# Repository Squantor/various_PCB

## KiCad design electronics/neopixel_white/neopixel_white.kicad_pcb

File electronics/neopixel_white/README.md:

# Neopixel formfactor white LED
Simple white led in neopixel form factor. Sometimes you dont want a controllable RGB LED in some spots.
## TODO's
Still some things need to be done:
* update Readme.md with pictures and BOM
## BOM
* Generic white LED in 2835 package

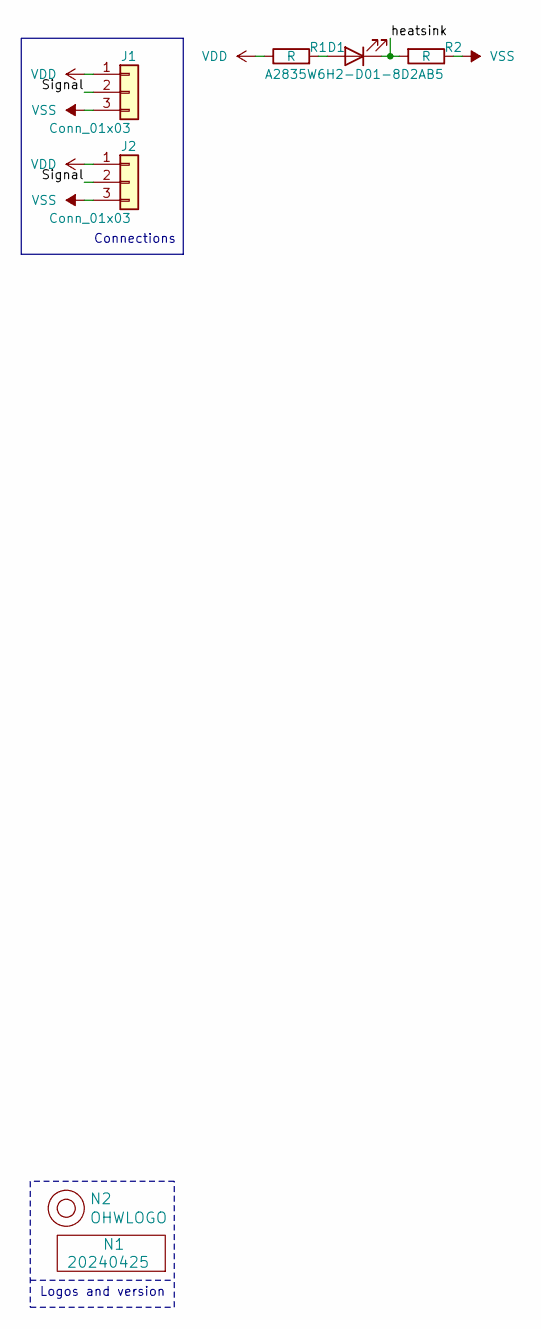
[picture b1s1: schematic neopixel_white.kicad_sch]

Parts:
D1: A2835W6H2-D01-8D2AB5; LED_2835_Hongli
J1, J2: Conn_01x03; pads-0200-1x03-W012-D020
N1: 20240425; Label_Generic
N2: OHWLOGO; OSHW-Symbol_6.7x6mm_SilkScreen
R1, R2: R; R_0805

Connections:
/Signal: J1.2, J2.2
/heatsink: D1.1 (K), R2.2
unnamed: D1.2 (A), R1.2
VDD: J1.1, J2.1, R1.1
VSS: J1.3, J2.3, R2.1

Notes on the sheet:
Connections
Logos and version

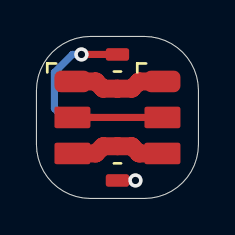
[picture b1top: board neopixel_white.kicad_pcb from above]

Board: 2 copper layers, 9.0 x 9.0 mm, 7 parts (1 on the bottom side), 5 nets.

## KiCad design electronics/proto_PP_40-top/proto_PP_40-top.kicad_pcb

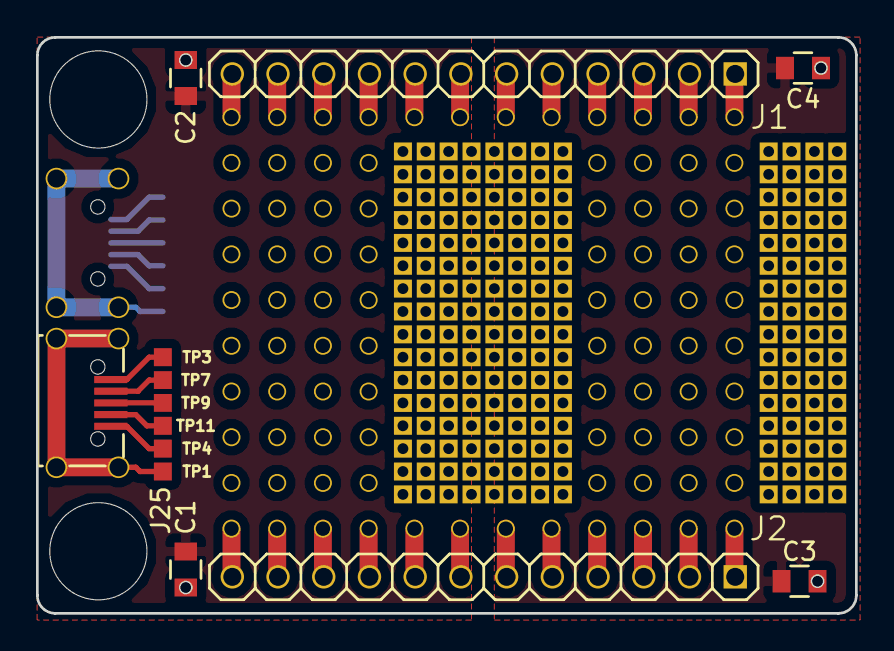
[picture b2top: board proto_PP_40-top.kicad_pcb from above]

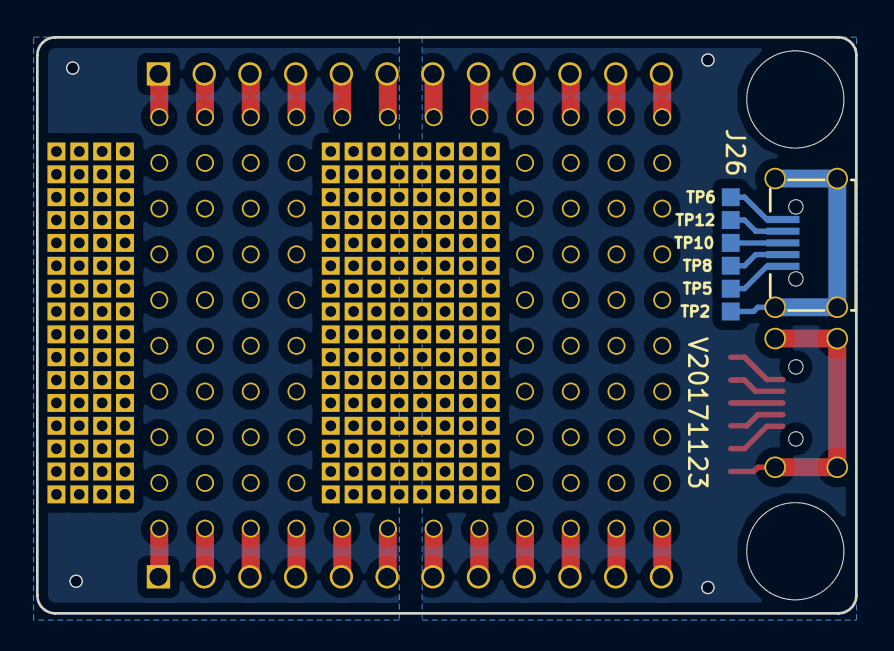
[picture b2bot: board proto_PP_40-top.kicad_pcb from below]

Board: 2 copper layers, 45.5 x 32.0 mm, 45 parts (8 on the bottom side), 40 nets.

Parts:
C1, C2, C3, C4: C; C_0805
H1, H2: Drill_Hole_no_metal; MountingHole_5.4mm_no_metal
J1, J2: PINS_1X12; Header-0254-1X12-H010
J3, J4, J7, J18, J19, J20: Proto_4pins; proto-TH-0254-04X01-P010SQ-H008
J5, J6, J9, J10, J13, J14, J16, J17, J21, J22, J23, J24: Proto; proto-SMD-0127-04X04-P010-H006
J8, J11, J12, J15: Proto; proto-TH-0254-04X04-P010SQ-H008
J25, J26: USB-ID; SquantorUsb-USB-UB-SMD4H
N2: V20171123; Label_version
TP1, TP2, TP3, TP4, TP5, TP6, TP7, TP8, TP9, TP10, TP11, TP12: testpad; TESTPAD_SQ_1MM

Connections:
GND: C1.2, C2.2
GNDA: C3.2, C4.2
unnamed: J1.1, J3.1
unnamed: J1.2, J3.2
unnamed: J1.3, J3.3
unnamed: J1.4, J3.4
unnamed: J1.5, J7.1
unnamed: J1.6, J7.2
unnamed: J1.7, J7.3
unnamed: J1.8, J7.4
unnamed: J1.9, J4.1
unnamed: J1.10, J4.2
unnamed: J1.11, J4.3
unnamed: J1.12, J4.4
unnamed: J2.9, J20.1
unnamed: J2.10, J20.2
unnamed: J2.11, J20.3
unnamed: J2.12, J20.4
unnamed: J2.5, J18.1
unnamed: J2.6, J18.2
unnamed: J2.7, J18.3
unnamed: J2.8, J18.4
unnamed: J2.1, J19.1
unnamed: J2.2, J19.2
unnamed: J2.3, J19.3
unnamed: J2.4, J19.4
unnamed: J25.1, TP3.1
unnamed: J25.2, TP7.1
unnamed: J25.3, TP9.1
unnamed: J25.4, TP11.1
unnamed: J25.5, TP4.1
unnamed: J25.S, TP1.1
unnamed: J26.1, TP5.1
unnamed: J26.2, TP8.1
unnamed: J26.3, TP10.1
unnamed: J26.4, TP12.1
unnamed: J26.5, TP6.1
unnamed: J26.S, TP2.1
VDD: C1.1, C2.1
VDDA: C3.1, C4.1

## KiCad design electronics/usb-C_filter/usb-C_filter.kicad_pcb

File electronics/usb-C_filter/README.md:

# USB-C filter
USB style filter/protection prevents communication on data lines but can also be used as USB-C to USB-A converter.
## TODO's
Still some things need to be done:
* schematic entry 
* PCB layout
* Review with one night in between
* Produce at [OSHPARK](https://oshpark.com/)
* Assemble
* Test & characterise
* update Readme.md with pictures and BOM
## BOM
* [USB-C connector from LCSC](https://lcsc.com/product-detail/USB-Connectors_Korean-Hroparts-Elec-TYPE-C-31-M-12_C165948.html)

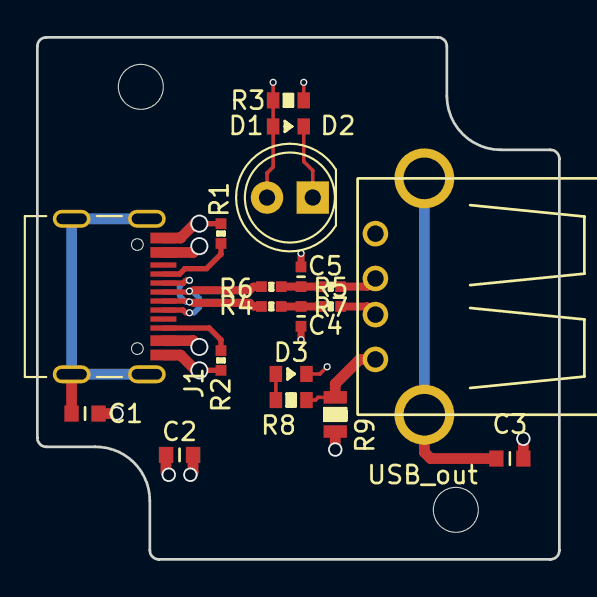
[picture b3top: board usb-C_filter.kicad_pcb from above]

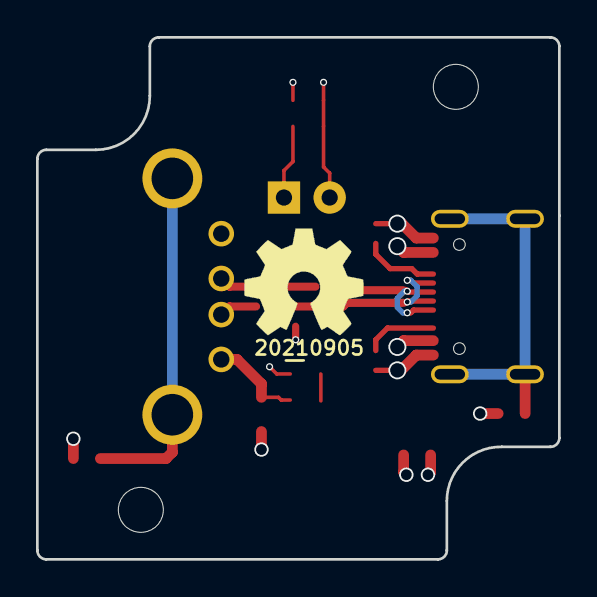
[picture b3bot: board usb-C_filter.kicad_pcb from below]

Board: 4 copper layers, 29.0 x 29.0 mm, 23 parts (2 on the bottom side), 15 nets.

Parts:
C1, C3: 10n; C_0603
C2: 100n; C_0603
C4, C5: TBD; C_0402
D1, D3: LED; LED_0603_hand
D2: LED; LED_D5.0mm
H1, H2: Drill_Hole_no_metal; MountingHole_2.5mm_no_metal
J1: USB-C_PD_USB; USB-C-HRO-31-M-12
J2: USB_out; USB-A-TH
N1: OHWLOGO; OSHW-Symbol_6.7x6mm_SilkScreen
N2: 20210905; Label_Generic
R1, R2: 5.1K; R_0402_hand
R3, R8: 1K; R_0603_hand
R4, R5, R6, R7: TBD; R_0402_hand
R9: 0; R_0805

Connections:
/CC1: J1.A5, R1.2
/CC2: J1.B5, R2.2
/DN_out: J2.2, R5.2
/DP_out: J2.3, R7.2
/Din+: J1.A6, J1.B6, R6.2
/Din-: J1.A7, J1.B7, R4.2
/GND: C1.2, C2.2, C3.2, C4.2, C5.2, D1.1, D2.1, D3.1, J1.A1B12, J1.B1A12, J2.4, R1.1, R2.1
/VBUS: C2.1, J1.A4B9, J1.B4A9, R3.1, R9.2
/VBUS_in: J2.1, R8.1, R9.1
unnamed: C1.1, J1.S
unnamed: C3.1, J2.S
unnamed: C4.1, R4.1, R5.1
unnamed: C5.1, R6.1, R7.1
unnamed: D1.2, D2.2, R3.2
unnamed: D3.2, R8.2

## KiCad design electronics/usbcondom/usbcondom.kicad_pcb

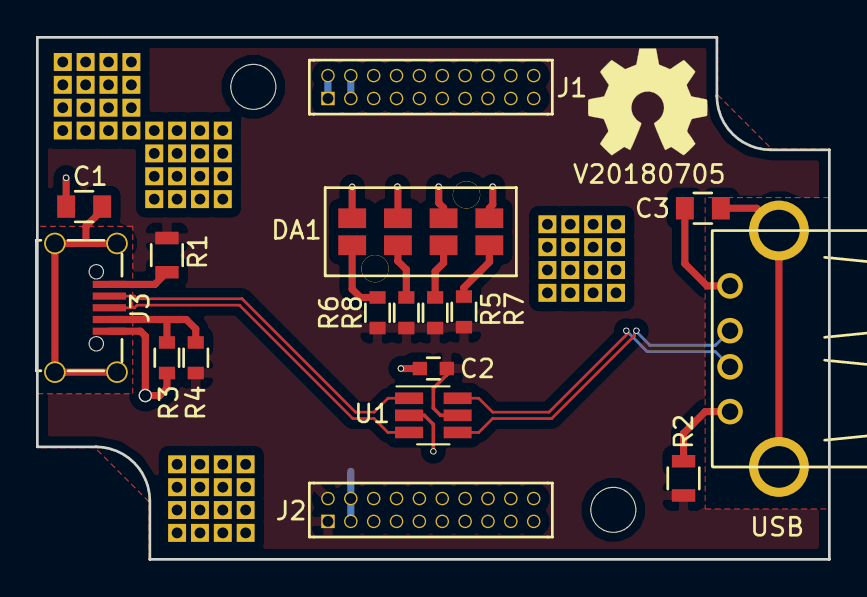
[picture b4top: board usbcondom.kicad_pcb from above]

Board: 2 copper layers, 44.0 x 29.0 mm, 25 parts (0 on the bottom side), 17 nets.

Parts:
C1, C3: C; C_0805
C2: 100n; C_0603
DA1: mentor_1296.4124
H1, H2: Drill_Hole_no_metal; MountingHole_2.5mm_no_metal
J1, J2: Conn_02x10_Odd_Even; Header-0127-2X10-H006
J3: USB-ID; USB-muB-SMD_TH
J4: USB; USB-A-TH
J5, J6, J7, J8: Proto; proto-SMD-0127-04X04-P010-H006
N1: OHWLOGO; OSHW-Symbol_6.7x6mm_SilkScreen
N2: V20180705; Label_version
R1, R2: FB; R_0805
R3, R4, R5, R6, R7, R8: R; R_0603_hand
U1: USBLC6-2; SOT-23-6_Handsoldering

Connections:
/USB_IN_D+: J3.3, U1.3
/USB_IN_D-: J3.2, U1.1
/USB_OUT_D+: J4.3, U1.4
/USB_OUT_D-: J4.2, U1.6
unnamed: C1.2, J3.S
unnamed: C3.2, J4.S
unnamed: DA1.1, R7.1
unnamed: DA1.2, R5.1
unnamed: DA1.3, R8.1
unnamed: DA1.4, R6.1
unnamed: J3.1, R1.2
unnamed: J3.4, R3.1, R4.1
unnamed: J4.1, R2.1
VDD: C2.2, J2.1, J2.2, R1.1, R2.2, R4.2, R5.2, R6.2, R7.2, R8.2, U1.5
VDDA: J1.1, J1.2
VSS: C1.1, C2.1, C3.1, DA1.5, DA1.6, DA1.7, DA1.8, J2.3, J2.4, J3.5, J4.4, R3.2, U1.2
VSSA: J1.3, J1.4

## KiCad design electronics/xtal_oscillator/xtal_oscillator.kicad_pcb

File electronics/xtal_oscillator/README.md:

# Crystal oscillator
Small crystal oscillator PCB using the 1GX04 style pierce oscillator and driver logic IC. You can get the PCB from [OSHpark](https://oshpark.com/shared_projects/tEdkEFkm).
## TODO's
All finished!
## Usage
Most of the information here is taken from various datasheets from [Nexperia](https://assets.nexperia.com/documents/data-sheet/74LVC1GX04.pdf) and [Texas instruments](https://www.ti.com/product/SN74LVC1GX04).

### Rf
The feedback resistor needs to be high ohmic, for me it seems that 10MegOhms is sufficient, you can probably lower it. 
Nexperia has a good test procedure to prevent spurious oscillations by testing the circuit without a crystal and checking of nothing oscillates. This makes sure you have enough gain for oscillation but not for any spurious oscillations to occur.
### C1 and C2
The predominant formula seems to be like this:

### Rs
Rs is tricky, the datasheets recommend that you compute the impedance of C2 at the oscillation frequency to create a 50% divider with Rs. This seems to work for normal AT cut crystals.

But this does not work well for tuningfork crystals like those of 32.768KHz. Another rule of thumb I have read is to take the ESR and multiply it by 4. I am not sure where I got that one but does seem to do the trick for the tuning fork types.
### Example table
Crystal|Rf|C1 & C2| Rs|Frequency
-------|--|-------|---|---------
[Q13FC13500004 FC-135 32.768KHZ 12.5PF](http://www.farnell.com/datasheets/2018173.pdf)|10Mohm|15pF|220KOhm(see notes)|32.768KHz
[MCSJK-7U-12.00-12-30-80-B-30](http://www.farnell.com/datasheets/2864166.pdf)|10Mohm|15pF|100Ohm|12MHz
[XTY 7216-2500A2010-00 ](https://lcsc.com/product-detail/New-Arrivals_XTY-7216-2500A2010-00_C389792.html)|10MOhm|33pF|300Ohm|25MHz
[XRCGB32M000F2P10R0](https://www.murata.com/products/productdata/8801079492638/SPEC-XRCGB32M000F2P10R0.pdf)|10MOhm|4.7pF|1KOhm|32MHz

## BOM
* Any crystal in 3225 housing, you can also fit smaller crystals in that same footprint with some positioning
* any 1GX04 chip from nexperia or TI
* 0603/0805 high ohmic feedback resistor
* All other passives 0402
# Pictures

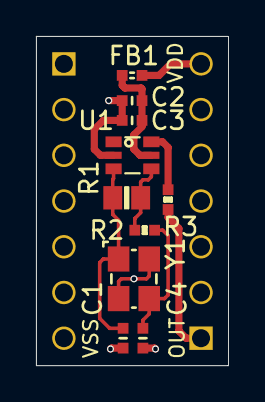
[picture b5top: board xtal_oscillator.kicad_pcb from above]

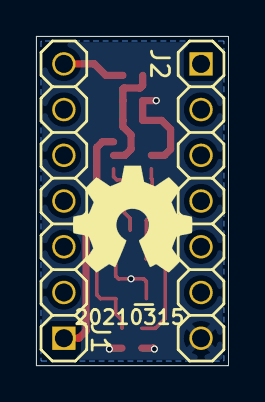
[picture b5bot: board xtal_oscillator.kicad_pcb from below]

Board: 2 copper layers, 10.7 x 18.3 mm, 14 parts (4 on the bottom side), 8 nets.

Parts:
C1, C4: TBD; C_0402
C2: 1u; C_0402
C3: 100n; C_0402
FB1: 600; L_0402
J1, J2: Conn_01x07; Header-0254-1X07-H010
N1: 20210315; Label_Generic
N2: OHWLOGO; OSHW-Symbol_6.7x6mm_SilkScreen
R1: Rf; R_0805+0603
R2: Rs; R_0402_hand
R3: 100; R_0402_hand
U1: 74X1GX04; SOT363-hand
Y1: Any; Crystal_3225_4

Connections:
/OUT: J1.1, R3.1
/VDD: FB1.1, J1.7
/VDD_int: C2.1, C3.1, FB1.2, U1.5
/VSS: C1.2, C2.2, C3.2, C4.2, J2.7, U1.2, Y1.2, Y1.4
unnamed: C1.1, R1.2, U1.3, Y1.1
unnamed: C4.1, R2.1, Y1.3
unnamed: R1.1, R2.2, U1.4
unnamed: R3.2, U1.6

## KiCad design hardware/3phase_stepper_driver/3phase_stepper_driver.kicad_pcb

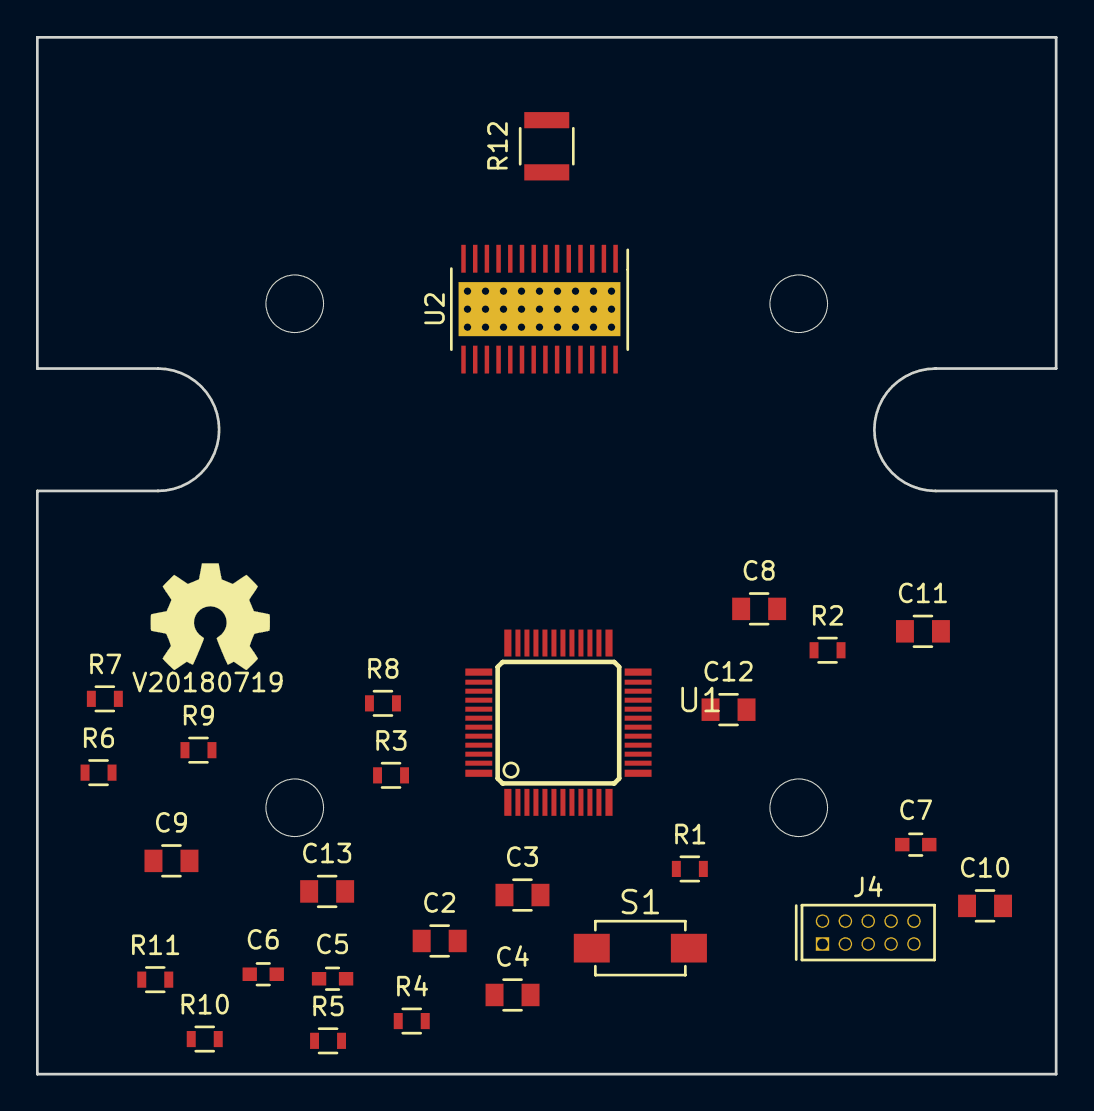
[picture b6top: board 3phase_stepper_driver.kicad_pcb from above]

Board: 2 copper layers, 56.6 x 57.6 mm, 34 parts (0 on the bottom side), 20 nets, no tracks yet.

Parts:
C2, C3, C4, C11: 10u; C_0805
C5, C6, C7: 100n; C_0603
C8: 10n; C_0805
C9, C12, C13: 100n; C_0805
C10: 470n; C_0805
H1, H2, H3, H4: Drill_Hole_no_metal; MountingHole_3.2mm_no_metal
J4: JTAG_2X05; Header-0127-2X05-H006
N1: OHWLOGO; OSHW-Symbol_6.7x6mm_SilkScreen
N2: V20180719; Label_version
R1, R2, R3, R10: 10K; R_0603
R4, R5, R6, R7, R8: 100; R_0603
R9: 10; R_0603
R11: 1K; R_0603
R12: 0.1; R_1210
S1: 2pin_tact_switch; DTSM3
U1: LPC845M301JBD48; SOT313-2
U2: DRV8313; HTSSOP-28_-TexasInstruments_PWP

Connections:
/RESET: R1.2, R7.2, S1.1, U1.5
/SENSE_I: R12.1, U2.6, U2.7, U2.10, U2.12
/SENSE_REF: R10.1, R11.2, U2.13
/SWDCLK: R2.2, R4.2
/SWDIO: R3.2, R6.2, U1.10
/VREF: C2.1, C5.1, U1.32
GNDPWR: C10.1, C11.2, C12.2, C13.2, R12.2, U2.14, U2.20, U2.28, U2.PAD
unnamed: C8.1, U2.1
unnamed: C8.2, U2.2
unnamed: C9.1, U2.3
unnamed: C10.2, U2.15
unnamed: J4.1, R9.2
unnamed: J4.2, R6.1
unnamed: J4.4, R4.1
unnamed: J4.10, R7.1
VCC: C9.2, C11.1, C12.1, C13.1, U2.4, U2.11
VDD: C3.1, C6.1, R1.1, R3.1, R9.1, U1.29
VDDA: C4.1, C7.1, U1.40
VSS: C3.2, C6.2, J4.3, J4.5, J4.9, R2.1, S1.2, U1.30
VSSA: C2.2, C4.2, C5.2, C7.2, R11.1, U1.31, U1.41
